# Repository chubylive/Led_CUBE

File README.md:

Led_CUBE
========

rgb led cube

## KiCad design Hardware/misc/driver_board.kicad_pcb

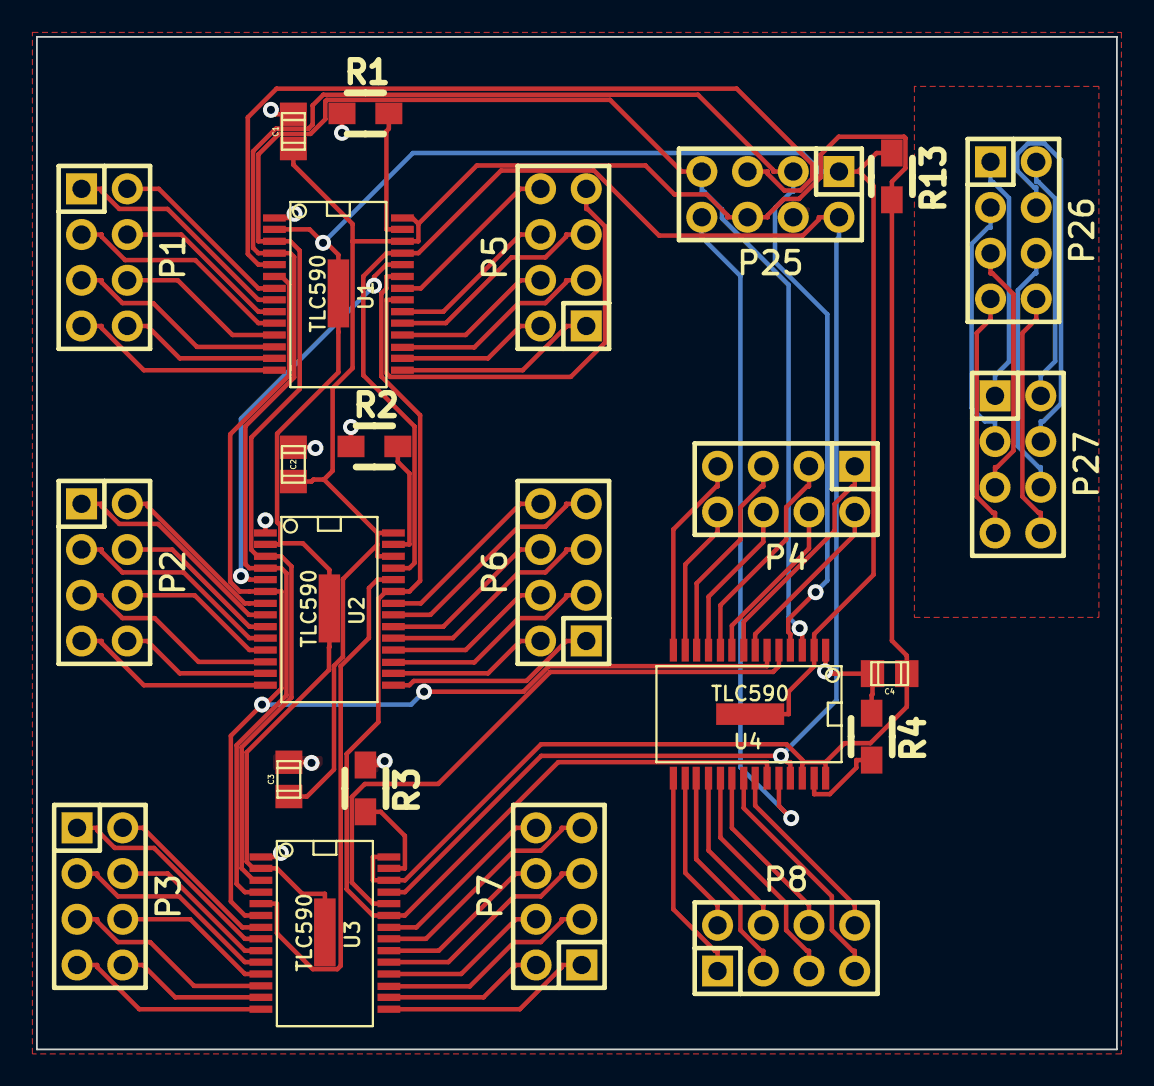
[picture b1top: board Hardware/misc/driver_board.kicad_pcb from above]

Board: 2 copper layers, 60.0 x 56.2 mm, 24 parts (0 on the bottom side), 89 nets.

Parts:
C1, C2, C3, C4: C; c_0805
P1, P2, P3, P4, P5, P6, P7, P8, P25, P26, P27: CONN_4X2; Pin_Header_Straight_2x04
R1, R2, R3, R4, R13: R; Resistor_SMD0805_HandSoldering
U1, U2, U3, U4: TLC590; SSOP-28H

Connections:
+3.3V: C1.2, C2.2, C3.2, C4.2, P25.6, R13.2, U1.26, U1.28, U2.26, U2.28, U3.26, U3.28, U4.26, U4.28
/L1: P26.1, P27.1
/L2: P26.2, P27.2
/L3: P26.3, P27.3
/L4: P26.4, P27.4
/L5: P26.5, P27.5
/L6: P26.6, P27.6
/L7: P26.7, P27.7
/L8: P26.8, P27.8
/ROA1: P1.2, U1.7
/ROA2: P1.1, U1.8
/ROA3: P1.4, U1.9
/ROA4: P1.3, U1.10
/ROA5: P1.6, U1.11
/ROA6: P1.5, U1.12
/ROA7: P1.8, U1.13
/ROA8: P1.7, U1.14
/ROA9: P5.1, U1.15
/ROA10: P5.2, U1.16
/ROA11: P5.3, U1.17
/ROA12: P5.4, U1.18
/ROA13: P5.5, U1.19
/ROA14: P5.6, U1.20
/ROA15: P5.7, U1.21
/ROA16: P5.8, U1.22
/ROB1: P2.2, U2.7
/ROB2: P2.1, U2.8
/ROB3: P2.4, U2.9
/ROB4: P2.3, U2.10
/ROB5: P2.6, U2.11
/ROB6: P2.5, U2.12
/ROB7: P2.8, U2.13
/ROB8: P2.7, U2.14
/ROB9: P6.1, U2.15
/ROB10: P6.2, U2.16
/ROB11: P6.3, U2.17
/ROB12: P6.4, U2.18
/ROB13: P6.5, U2.19
/ROB14: P6.6, U2.20
/ROB15: P6.7, U2.21
/ROB16: P6.8, U2.22
/ROC1: P3.2, U3.7
/ROC2: P3.1, U3.8
/ROC3: P3.4, U3.9
/ROC4: P3.3, U3.10
/ROC5: P3.6, U3.11
/ROC6: P3.5, U3.12
/ROC7: P3.8, U3.13
/ROC8: P3.7, U3.14
/ROC9: P7.1, U3.15
/ROC10: P7.2, U3.16
/ROC11: P7.3, U3.17
/ROC12: P7.4, U3.18
/ROC13: P7.5, U3.19
/ROC14: P7.6, U3.20
/ROC15: P7.7, U3.21
/ROC16: P7.8, U3.22
/ROD1: P4.2, U4.7
/ROD2: P4.1, U4.8
/ROD3: P4.4, U4.9
/ROD4: P4.3, U4.10
/ROD5: P4.6, U4.11
/ROD6: P4.5, U4.12
/ROD7: P4.8, U4.13
/ROD8: P4.7, U4.14
/ROD9: P8.1, U4.15
/ROD10: P8.2, U4.16
/ROD11: P8.3, U4.17
/ROD12: P8.4, U4.18
/ROD13: P8.5, U4.19
/ROD14: P8.6, U4.20
/ROD15: P8.7, U4.21
/ROD16: P8.8, U4.22
/blank: P25.1, R13.1, U1.2, U2.2, U3.2, U4.2
/gsclk: P25.2, U1.25, U2.25, U3.25, U4.25
/sclk: P25.3, U1.4, U2.4, U3.4, U4.4
/sin: P25.5, U1.5
/sin_B: U1.24, U2.5
/sin_C: U2.24, U3.5
/sin_D: U3.24, U4.5
/sin_E: P25.8, U4.24
/vprg: U1.6, U2.6, U3.6, U4.6
/xerr: U1.23, U2.23, U3.23, U4.23
/xlat: P25.7, U1.3, U2.3, U3.3, U4.3
GND: C1.1, C2.1, C3.1, C4.1, P25.4, R1.1, R2.1, R3.1, R4.1, U1.1, U2.1, U3.1, U4.1
unnamed: R1.2, U1.27
unnamed: R2.2, U2.27
unnamed: R3.2, U3.27
unnamed: R4.2, U4.27

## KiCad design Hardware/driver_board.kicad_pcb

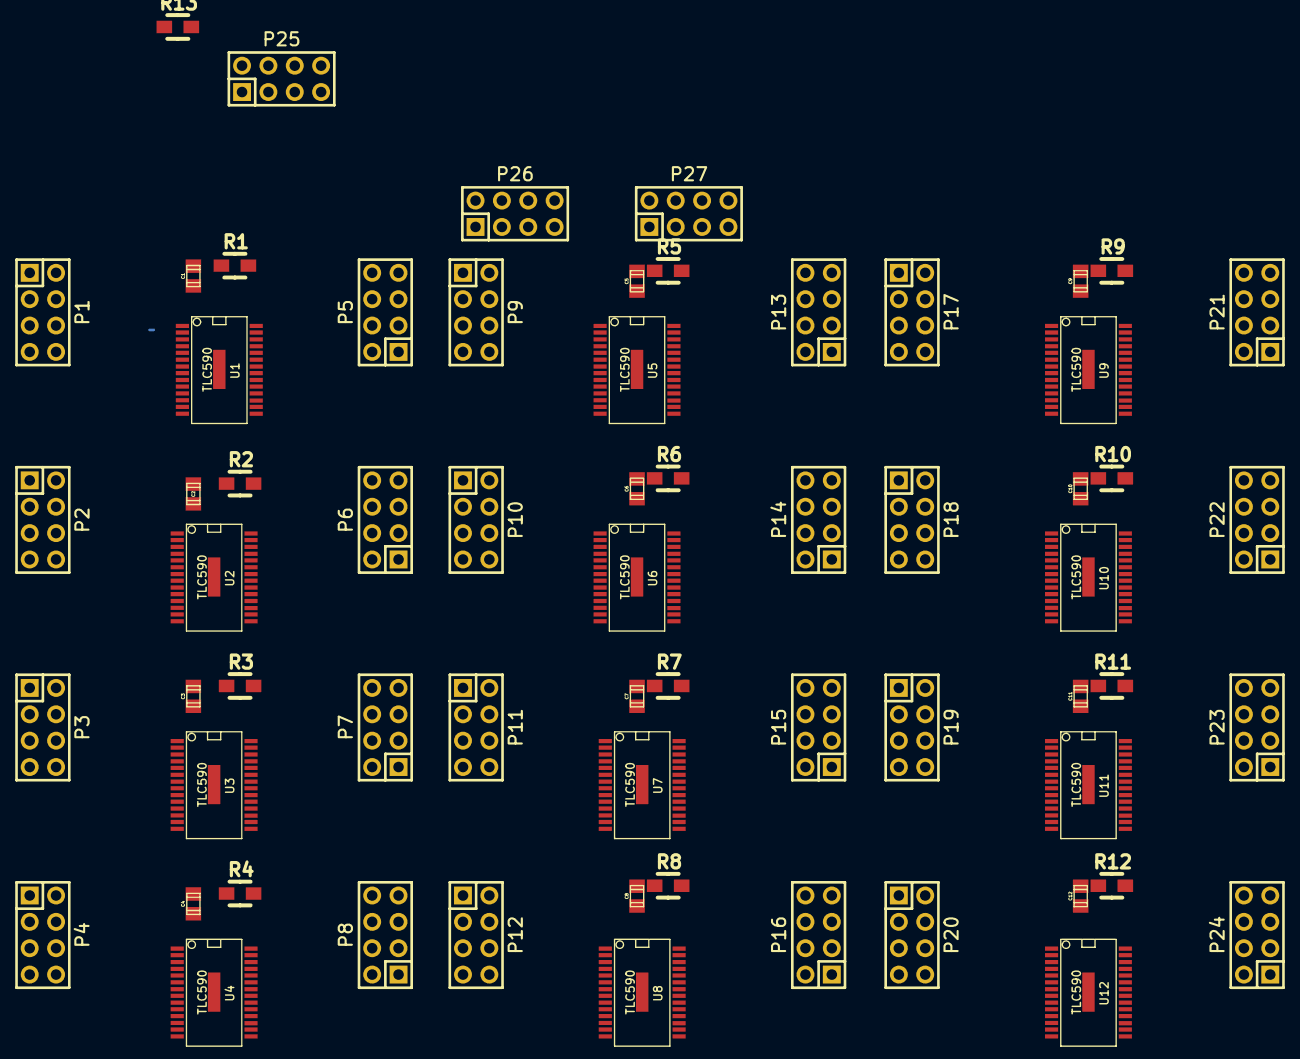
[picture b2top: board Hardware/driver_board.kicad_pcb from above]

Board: 2 copper layers, 64 parts (0 on the bottom side), 232 nets.

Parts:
C1, C2, C3, C4, C5, C6, C7, C8, C9, C10, C11, C12: C; c_0805
P1, P2, P3, P4, P5, P6, P7, P8, P9, P10, P11, P12, P13, P14, P15, P16, P17, P18, P19, P20, P21, P22, P23, P24, P25, P26, P27: CONN_4X2; Pin_Header_Straight_2x04
R1, R2, R3, R4, R5, R6, R7, R8, R9, R10, R11, R12, R13: R; Resistor_SMD0805_HandSoldering
U1, U2, U3, U4, U5, U6, U7, U8, U9, U10, U11, U12: TLC590; SSOP-28H

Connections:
+3.3V: C1.2, C2.2, C3.2, C4.2, C5.2, C6.2, C7.2, C8.2, C9.2, C10.2, C11.2, C12.2, P25.6, R13.2, U1.26, U1.28, U2.26, U2.28, U3.26, U3.28, U4.26, U4.28, U5.26, U5.28, U6.26, U6.28, U7.26, U7.28, U8.26, U8.28, U9.26, U9.28, U10.26, U10.28, U11.26, U11.28, U12.26, U12.28
/BOA1: P17.2, U9.7
/BOA2: P17.1, U9.8
/BOA3: P17.4, U9.9
/BOA4: P17.3, U9.10
/BOA5: P17.6, U9.11
/BOA6: P17.5, U9.12
/BOA7: P17.8, U9.13
/BOA8: P17.7, U9.14
/BOA9: P21.1, U9.15
/BOA10: P21.2, U9.16
/BOA11: P21.3, U9.17
/BOA12: P21.4, U9.18
/BOA13: P21.5, U9.19
/BOA14: P21.6, U9.20
/BOA15: P21.7, U9.21
/BOA16: P21.8, U9.22
/BOB1: P18.2, U10.7
/BOB2: P18.1, U10.8
/BOB3: P18.4, U10.9
/BOB4: P18.3, U10.10
/BOB5: P18.6, U10.11
/BOB6: P18.5, U10.12
/BOB7: P18.8, U10.13
/BOB8: P18.7, U10.14
/BOB9: P22.1, U10.15
/BOB10: P22.2, U10.16
/BOB11: P22.3, U10.17
/BOB12: P22.4, U10.18
/BOB13: P22.5, U10.19
/BOB14: P22.6, U10.20
/BOB15: P22.7, U10.21
/BOB16: P22.8, U10.22
/BOC1: P19.2, U11.7
/BOC2: P19.1, U11.8
/BOC3: P19.4, U11.9
/BOC4: P19.3, U11.10
/BOC5: P19.6, U11.11
/BOC6: P19.5, U11.12
/BOC7: P19.8, U11.13
/BOC8: P19.7, U11.14
/BOC9: P23.1, U11.15
/BOC10: P23.2, U11.16
/BOC11: P23.3, U11.17
/BOC12: P23.4, U11.18
/BOC13: P23.5, U11.19
/BOC14: P23.6, U11.20
/BOC15: P23.7, U11.21
/BOC16: P23.8, U11.22
/BOD1: P20.2, U12.7
/BOD2: P20.1, U12.8
/BOD3: P20.4, U12.9
/BOD4: P20.3, U12.10
/BOD5: P20.6, U12.11
/BOD6: P20.5, U12.12
/BOD7: P20.8, U12.13
/BOD8: P20.7, U12.14
/BOD9: P24.1, U12.15
/BOD10: P24.2, U12.16
/BOD11: P24.3, U12.17
/BOD12: P24.4, U12.18
/BOD13: P24.5, U12.19
/BOD14: P24.6, U12.20
/BOD15: P24.7, U12.21
/BOD16: P24.8, U12.22
/GOA1: P9.2, U5.7
/GOA2: P9.1, U5.8
/GOA3: P9.4, U5.9
/GOA4: P9.3, U5.10
/GOA5: P9.6, U5.11
/GOA6: P9.5, U5.12
/GOA7: P9.8, U5.13
/GOA8: P9.7, U5.14
/GOA9: P13.1, U5.15
/GOA10: P13.2, U5.16
/GOA11: P13.3, U5.17
/GOA12: P13.4, U5.18
/GOA13: P13.5, U5.19
/GOA14: P13.6, U5.20
/GOA15: P13.7, U5.21
/GOA16: P13.8, U5.22
/GOB1: P10.2, U6.7
/GOB2: P10.1, U6.8
/GOB3: P10.4, U6.9
/GOB4: P10.3, U6.10
/GOB5: P10.6, U6.11
/GOB6: P10.5, U6.12
/GOB7: P10.8, U6.13
/GOB8: P10.7, U6.14
/GOB9: P14.1, U6.15
/GOB10: P14.2, U6.16
/GOB11: P14.3, U6.17
/GOB12: P14.4, U6.18
/GOB13: P14.5, U6.19
/GOB14: P14.6, U6.20
/GOB15: P14.7, U6.21
/GOB16: P14.8, U6.22
/GOC1: P11.2, U7.7
/GOC2: P11.1, U7.8
/GOC3: P11.4, U7.9
/GOC4: P11.3, U7.10
/GOC5: P11.6, U7.11
/GOC6: P11.5, U7.12
/GOC7: P11.8, U7.13
/GOC8: P11.7, U7.14
/GOC9: P15.1, U7.15
/GOC10: P15.2, U7.16
/GOC11: P15.3, U7.17
/GOC12: P15.4, U7.18
/GOC13: P15.5, U7.19
/GOC14: P15.6, U7.20
/GOC15: P15.7, U7.21
/GOC16: P15.8, U7.22
/GOD1: P12.2, U8.7
/GOD2: P12.1, U8.8
/GOD3: P12.4, U8.9
/GOD4: P12.3, U8.10
/GOD5: P12.6, U8.11
/GOD6: P12.5, U8.12
/GOD7: P12.8, U8.13
/GOD8: P12.7, U8.14
/GOD9: P16.1, U8.15
/GOD10: P16.2, U8.16
/GOD11: P16.3, U8.17
/GOD12: P16.4, U8.18
/GOD13: P16.5, U8.19
/GOD14: P16.6, U8.20
/GOD15: P16.7, U8.21
/GOD16: P16.8, U8.22
/L1: P26.1, P27.1
/L2: P26.2, P27.2
/L3: P26.3, P27.3
/L4: P26.4, P27.4
/L5: P26.5, P27.5
/L6: P26.6, P27.6
/L7: P26.7, P27.7
/L8: P26.8, P27.8
/ROA1: P1.2, U1.7
/ROA2: P1.1, U1.8
/ROA3: P1.4, U1.9
/ROA4: P1.3, U1.10
/ROA5: P1.6, U1.11
/ROA6: P1.5, U1.12
/ROA7: P1.8, U1.13
/ROA8: P1.7, U1.14
/ROA9: P5.1, U1.15
/ROA10: P5.2, U1.16
/ROA11: P5.3, U1.17
/ROA12: P5.4, U1.18
/ROA13: P5.5, U1.19
/ROA14: P5.6, U1.20
/ROA15: P5.7, U1.21
/ROA16: P5.8, U1.22
/ROB1: P2.2, U2.7
/ROB2: P2.1, U2.8
/ROB3: P2.4, U2.9
/ROB4: P2.3, U2.10
/ROB5: P2.6, U2.11
/ROB6: P2.5, U2.12
/ROB7: P2.8, U2.13
/ROB8: P2.7, U2.14
/ROB9: P6.1, U2.15
/ROB10: P6.2, U2.16
/ROB11: P6.3, U2.17
/ROB12: P6.4, U2.18
/ROB13: P6.5, U2.19
/ROB14: P6.6, U2.20
/ROB15: P6.7, U2.21
/ROB16: P6.8, U2.22
/ROC1: P3.2, U3.7
/ROC2: P3.1, U3.8
/ROC3: P3.4, U3.9
/ROC4: P3.3, U3.10
/ROC5: P3.6, U3.11
/ROC6: P3.5, U3.12
/ROC7: P3.8, U3.13
/ROC8: P3.7, U3.14
/ROC9: P7.1, U3.15
/ROC10: P7.2, U3.16
/ROC11: P7.3, U3.17
/ROC12: P7.4, U3.18
/ROC13: P7.5, U3.19
/ROC14: P7.6, U3.20
/ROC15: P7.7, U3.21
/ROC16: P7.8, U3.22
/ROD1: P4.2, U4.7
/ROD2: P4.1, U4.8
/ROD3: P4.4, U4.9
/ROD4: P4.3, U4.10
/ROD5: P4.6, U4.11
/ROD6: P4.5, U4.12
/ROD7: P4.8, U4.13
/ROD8: P4.7, U4.14
/ROD9: P8.1, U4.15
/ROD10: P8.2, U4.16
/ROD11: P8.3, U4.17
/ROD12: P8.4, U4.18
/ROD13: P8.5, U4.19
/ROD14: P8.6, U4.20
/ROD15: P8.7, U4.21
/ROD16: P8.8, U4.22
/blank: P25.1, R13.1, U1.2, U2.2, U3.2, U4.2, U5.2, U6.2, U7.2, U8.2, U9.2, U10.2, U11.2, U12.2
/gsclk: P25.2, U1.25, U2.25, U3.25, U4.25, U5.25, U6.25, U7.25, U8.25, U9.25, U10.25, U11.25, U12.25
/sclk: P25.3, U1.4, U2.4, U3.4, U4.4, U5.4, U6.4, U7.4, U8.4, U9.4, U10.4, U11.4, U12.4
/sin: P25.5, U1.5
/sin_B: U1.24, U2.5
/sin_C: U2.24, U3.5
/sin_D: U3.24, U4.5
/sin_E: U4.24, U5.5
/sin_F: U5.24, U6.5
/sin_G: U6.24, U7.5
/sin_H: U7.24, U8.5
/sin_I: U8.24, U9.5
/sin_J: U9.24, U10.5
/sin_K: U10.24, U11.5
/sin_L: U11.24, U12.5
/vprg: U1.6, U2.6, U3.6, U4.6, U5.6, U6.6, U7.6, U8.6, U9.6, U10.6, U11.6, U12.6
/xerr: U1.23, U2.23, U3.23, U4.23, U5.23, U6.23, U7.23, U8.23, U9.23, U10.23, U11.23, U12.23
/xlat: P25.7, U1.3, U2.3, U3.3, U4.3, U5.3, U6.3, U7.3, U8.3, U9.3, U10.3, U11.3, U12.3
GND: C1.1, C2.1, C3.1, C4.1, C5.1, C6.1, C7.1, C8.1, C9.1, C10.1, C11.1, C12.1, P25.4, R1.1, R2.1, R3.1, R4.1, R5.1, R6.1, R7.1, R8.1, R9.1, R10.1, R11.1, R12.1, U1.1, U2.1, U3.1, U4.1, U5.1, U6.1, U7.1, U8.1, U9.1, U10.1, U11.1, U12.1
unnamed: R1.2, U1.27
unnamed: R2.2, U2.27
unnamed: R3.2, U3.27
unnamed: R4.2, U4.27
unnamed: R5.2, U5.27
unnamed: R6.2, U6.27
unnamed: R7.2, U7.27
unnamed: R8.2, U8.27
unnamed: R9.2, U9.27
unnamed: R10.2, U10.27
unnamed: R11.2, U11.27
unnamed: R12.2, U12.27

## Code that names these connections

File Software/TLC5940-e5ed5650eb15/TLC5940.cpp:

#include "TLC5940.h"

TLC5940::TLC5940(PinName SCLK, PinName MOSI, PinName GSCLK, PinName BLANK, 
                 PinName XLAT, PinName DCPRG, PinName VPRG, const int number) : number(number),
                                                                                spi(MOSI, NC, SCLK),
                                                                                gsclk(GSCLK),
                                                                                blank(BLANK),
                                                                                xlat(XLAT),
                                                                                dcprg(DCPRG),
                                                                                vprg(VPRG),
                                                                                newGSData(false),
                                                                                newDCData(false),
                                                                                need_xlat(false)
{   
    // Configure SPI to 12 bits and SPI_SPEED
    spi.format(12, 0);
    spi.frequency(SPI_SPEED);
    
    // Set output pin states
    dcprg = 0;
    vprg = 0;
    xlat = 0;
    blank = 1;
    
    // Call the reset function every 4096 PWM outputs
    reset_ticker.attach_us(this, &TLC5940::reset, (1000000.0/GSCLK_SPEED) * 4096.0);
    
    // Configure FastPWM output for GSCLK frequency at 50% duty cycle
    gsclk.period_us(1000000.0/(GSCLK_SPEED * 1.05));
    gsclk.write(.5);
}

void TLC5940::setNewGSData(unsigned short* data)
{
    gsBuffer = data;
    
    // Tell reset function that new GS data has been given
    newGSData = true;
}

void TLC5940::setNewDCData(unsigned char* data)
{
    dcBuffer = data;
    
    // Tell reset function that new DC data has been given
    newDCData = true;
}

void TLC5940::reset()
{
    gsclk.write(0);
    // Turn off LEDs
    blank = 1;
    
    // Virtual function that allows the next data chunk to be set after every GSCLK cycle
    // Useful for setting the next frame when multiplexing (e.g. LED matrices)
    setNextData();
    
    // Latch in data from previous cycle if needed
    if (need_xlat)
    {
        // Latch
        xlat = 1;
        xlat = 0;
        
        // Don't need to latch again
        need_xlat = false;
    }
    
    // Reset the screen so that it is updating while data is being sent
    blank = 0;
    gsclk.write(.5);
    
    // Do we have new DC data to send?
    if (newDCData)
    {
        // Set TLC5940 to accpet DC data
        vprg = 1;
        
        // Get DC data from registers instead of EEPROM (since we are sending data to the registers now)
        dcprg = 1;
        
        // Send DC data backwards - this makes the DC_buffer[0] index correspond to OUT0
        for (int i = (16 * number) - 1; i >= 0; i--)
        {
            // Assemble a 12 bit packet from two 6 bit chunks
            spi.write(((dcBuffer[i] & 0x3F) << 6) | (dcBuffer[i-1] & 0x3F));
            i--;
        }
        
        // Latch
        xlat = 1;
        xlat = 0;
        
        // No new data to send (we just sent it!)
        newDCData = false;
    }
    
    // Do we have new GS data to send?
    if (newGSData)
    {
        // Set TLC5940 to accept GS data
        vprg = 0;
        
        // Send GS data backwards - this makes the GS_buffer[0] index correspond to OUT0 
        for (int i = (16 * number) - 1; i >= 0; i--)
        {
            // Get the lower 12 bits of the buffer and send
            spi.write(gsBuffer[i] & 0xFFF);
        }
        
        // Latch after current GS data is done being displayed
        need_xlat = true;
        
        // No new data to send (we just sent it!)
        newGSData = false;
    }
}

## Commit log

2014-06-20 first commit:
2014-06-21 starting
2014-06-24 half board
2014-08-04 please be cool
2014-08-06 progress
2014-08-07 good day
2014-08-28 driver done
2014-09-03 progress on board
2015-01-03 add corrected TLC54940 code what remains is to scale things up
2015-01-06 moving from kicad to eagle. The boards came ba ck with crazy shorts in them so i am re-designing them in kicad.
2015-01-07 just updated code on laptop
2015-02-01 a whole of stuff. got layers working. need to fix mux data buffer. figure out possible refresh rates
2015-02-08 implementing shift 16
2015-02-08 added new files not tested:
2015-02-18 testing of 16bit buffer complete. Creating new branch from which all dev would continue from and next would be mutiplexing buffer test. Then animation harness dev.
2015-02-18 16 bit shiftout
2015-02-18 8 bit base mux
2015-02-18 16 bit TLC5940_SetAllGS does not work
2015-02-27 strange things happening
2015-02-27 ghosting between two layers
2015-02-27 possible bug ing SetColour3D_16. It does not seem to set 2,*,*
2015-02-27 seem 8bit is indeed to slow
2015-02-28 break; was casuing ghosting
2015-03-01 animation started
2015-03-14 animation with single board success
2015-03-15 new colourwheel
2015-03-28 sinwave buggy
2015-04-08 current board files
2015-04-08 seems to be already updated V1 board files
2015-04-17 animation harness structs
2015-04-25 last changes before 4-24-2015 pull
2015-04-25 harness 1.0
2015-05-01 xor buffer for animation overlay
2015-05-02 xor buff working
2015-05-21 animation framework 1.0
2015-05-27 main board v2
2015-05-29 coming along
2015-08-17 adding eagle board 10mm*20mm
2016-01-27 new board complete
2016-05-09 added object hash not tested
2018-04-09 start in project please try to create a running log so retrancy is easy
2018-09-04 2018 changes
2018-09-05 sphere bounce
